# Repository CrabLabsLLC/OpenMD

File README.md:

# OpenMD

An Open Source Versatile Motor Driver powered by GaN

## Authors

[Orion Serup](orion@crablabs.io)

## Licensing

This project is licensed under the CERN Open Hardware License Version 2 - Weakly Reciprocal.

Different licensing can be provided for a nominal fee to allow for private spins of the design, contact the authors for more information on cost and license options.

## Operational Parameters

These are the initial estimates for reasonable limits provided sufficient cooling and stable power.

- Operating Voltage: 7V-80V
- Operating Current: 70A
- Max Theoretical Power: 4kW
- Switching Frequency: 50kHz-150KHz

## Purchasing

As of now this product is in Beta and thus is not publicly available for sale. Pre-production units may be available for evaluation, contact the authors for more information.

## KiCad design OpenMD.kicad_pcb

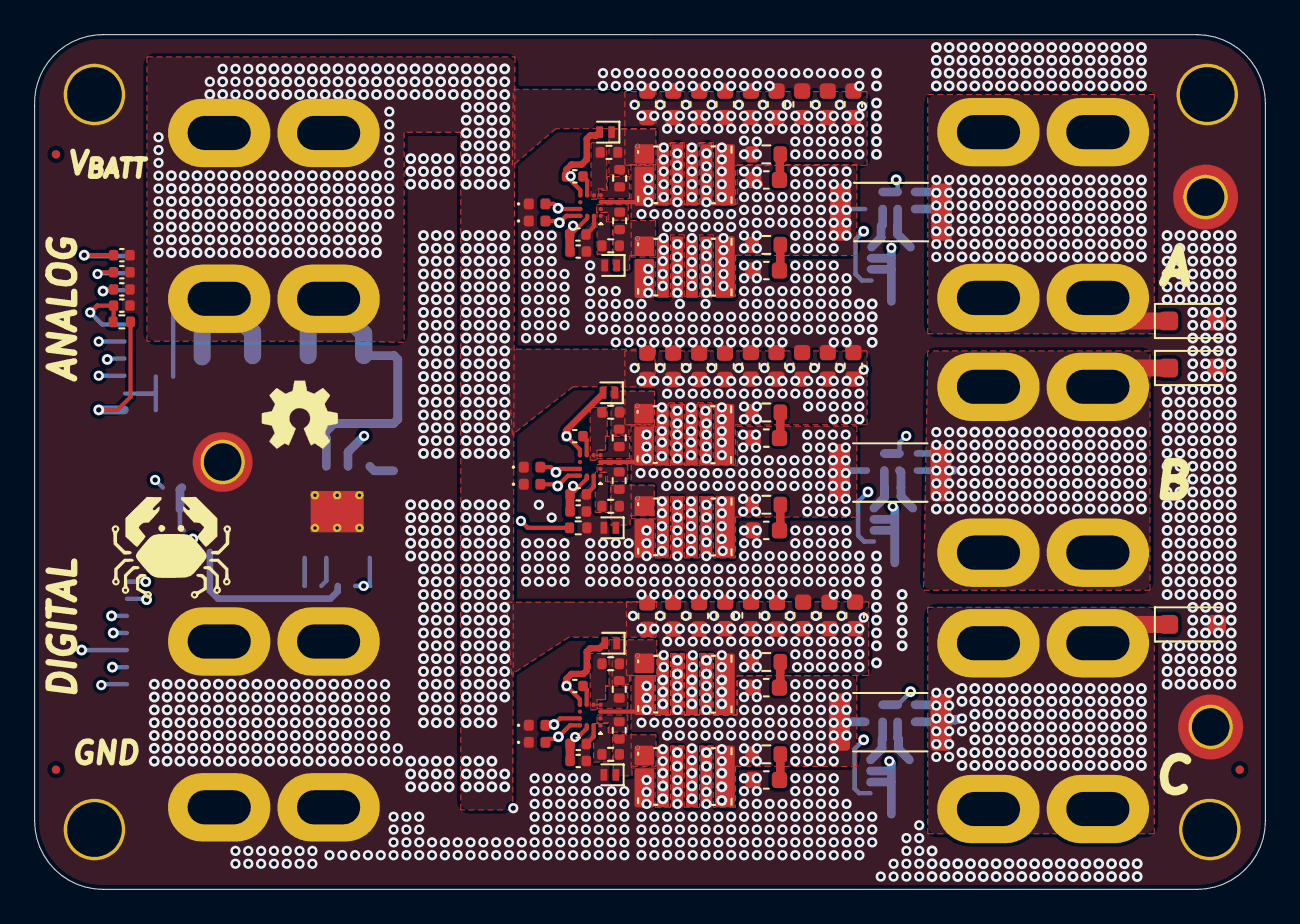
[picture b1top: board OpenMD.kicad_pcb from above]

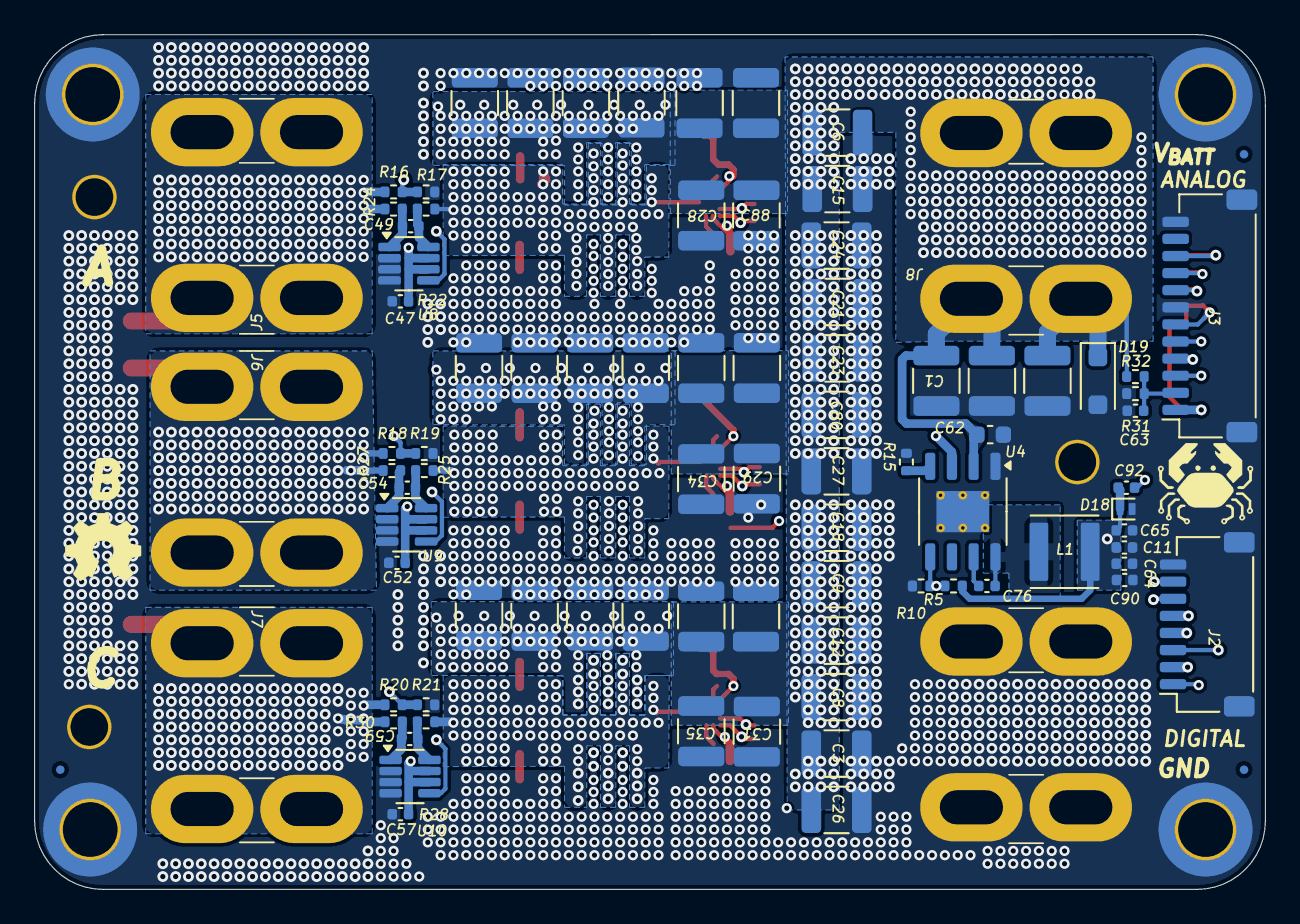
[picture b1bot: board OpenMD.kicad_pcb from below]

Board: 6 copper layers, 72.0 x 50.0 mm, 193 parts (93 on the bottom side), 62 nets.

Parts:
C1, C2, C3, C6, C7, C8, C9, C12, C15, C18, C19, C21, C23, C24, C26, C27, C78, C79, C80, C81, C82, C86, C87, C88, C89, C91, C93, C94, C98, C99, C100, C101, C102, C103: 10uF; C_1210_3225Metric
C4, C5, C10, C13, C14, C16, C17, C20, C22, C25, C30, C33, C36, C46, C48, C50, C51, C53, C55, C58, C60, C62, C70, C71, C72, C73, C74, C75: 100nF; C_0603_1608Metric
C11, C38, C39, C41, C42, C44, C45, C47, C52, C57, C63, C77: 100nF; C_0402_1005Metric
C28, C29, C31, C32, C34, C35: 4.7uF; C_1210_3225Metric
C37, C40, C43, C64, C65, C90: 4.7uF; C_0402_1005Metric
C49, C54, C59, C67, C68, C69: 10nF; C_0402_1005Metric
C56, C61, C66, C83, C84, C85: C; C_0603_1608Metric
C76: 2.2nF; C_0402_1005Metric
C92: 20pF; C_0402_1005Metric
D7, D8, D9, D19: 100V; D_SOD-123F
D12, D13, D14, D15, D16, D17: 5V; D_0402_1005Metric
D18, D27, D28, D29, D30, D31, D32: 6V; D_SOD-882
FID1, FID2, FID3, FID4, FID5, FID6: Fiducial; Fiducial_0.5mm_Mask1mm
H1, H2, H3, H4: M3; MountingHole_3.2mm_M3_ISO14580_Pad_TopOnly
H5: M2; MountingHole_2.2mm_M2_ISO7380_Pad_TopOnly
H6, H7: M2; MountingHole_2.2mm_M2_DIN965_Pad_TopOnly
J1: GND; DIP-4_252
J2: Digital; JST_SH_SM08B-SRSS-TB_1x08-1MP_P1.00mm_Horizontal
J3: Analog; JST_SH_SM12B-SRSS-TB_1x12-1MP_P1.00mm_Horizontal
J5: A; DIP-4_252
J6: B; DIP-4_252
J7: C; DIP-4_252
J8: V_{BATT}; DIP-4_252
L1: 68uH; L_Abracon_ASPI-4030S
Q1, Q2, Q3, Q4, Q5, Q6: EPC2361; D0606F_100V
R1, R4, R6, R9, R11, R14: 1; R_0402_1005Metric
R2, R3, R7, R8, R12, R13: 0; R_0402_1005Metric
R5, R16, R18, R20, R32: 240k; R_0402_1005Metric
R10: 72k; R_0402_1005Metric
R15: 27k; R_0402_1005Metric
R17, R19, R21, R31, R34: 10k; R_0402_1005Metric
R22, R24, R25, R27, R28, R30: 10; R_0402_1005Metric
R23, R26, R29: .5m; R_2512_6332Metric
R38, R39, R40, R41, R42, R43: R; R_0603_1608Metric
SYM1, SYM1#2: Logo_Open_Hardware_Large; OSHW-Symbol_8.9x8mm_SilkScreen
TH1: 10k NTC; R_0402_1005Metric
U1, U2, U3: LM1205; WLCSP1.6x1.6-12B_ECC
U4: LM5164DDA; HSOP-8-1EP_3.9x4.9mm_P1.27mm_EP2.41x3.1mm_ThermalVias
U8, U9, U10: INA241A2; SOT-23-8

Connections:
/A: D7.1 (K), J5.1, R16.1, R23.2, R24.1
/AH: D27.1 (K), Q4.1 (G), R3.2, R4.2
/AL: D30.1 (K), Q1.1 (G), R1.2, R2.1
/B: D8.1 (K), J6.1, R18.1, R26.2, R27.1
/BATT_SENSE: C63.1, J3.2, R31.1, R32.2
/BH: D28.1 (K), Q5.1 (G), R8.2, R9.2
/BL: D31.1 (K), Q2.1 (G), R6.2, R7.1
/C: D9.1 (K), J7.1, R20.1, R29.2, R30.1
/CH: D29.1 (K), Q6.1 (G), R13.2, R14.2
/CL: D32.1 (K), Q3.1 (G), R11.2, R12.1
/DRV_TEMP_SENSE: C77.1, J3.6, R34.2, TH1.1
/ENABLE: J2.1, U4.3 (EN/UVLO)
/GND: C1.2, C2.2, C3.2, C4.2, C5.2, C6.2, C7.2, C8.2, C9.2, C10.2, C11.2, C12.2, C13.2, C14.2, C15.2, C16.2, C17.2, C18.2, C19.2, C20.2, C21.2, C22.2, C23.2, C24.2, C25.2, C26.2, C27.2, C28.2, C29.2, C30.2, C31.2, C32.2, C33.2, C34.2, C35.2, C36.2, C37.2, C38.2, C40.2, C41.2, C43.2, C44.2, C46.2, C47.2, C48.2, C50.2, C51.2, C52.2, C53.2, C55.2, C57.2, C58.2, C60.2, C62.2, C63.2, C64.2, C65.2, C67.2, C68.2, C69.2, C70.2, C71.2, C72.2, C73.2, C74.2, C75.2, C77.2, C78.2, C79.2, C80.2, C81.2, C82.2, C83.2, C84.2, C85.2, C86.2, C87.2, C88.2, C89.2, C90.2, C91.2, C93.2, C94.2, C98.2, C99.2, C100.2, C101.2, C102.2, C103.2, D7.2 (A), D8.2 (A), D9.2 (A), D12.1 (A1), D13.1 (A1), D14.1 (A1), D15.1 (A1), D16.1 (A1), D17.1 (A1), D18.2 (A), D19.2 (A), D30.2 (A), D31.2 (A), D32.2 (A), H1.1, H2.1, H3.1, H4.1, H5.1, H6.1, H7.1, J1.1, J2.8, J2.MP (MountPin), J3.7, J3.12, J3.MP (MountPin), Q1.2 (S), Q1.4 (S), Q1.6 (S), Q2.2 (S), Q2.4 (S), Q2.6 (S), Q3.2 (S), Q3.4 (S), Q3.6 (S), R10.2, R15.2, R17.2, R19.2, R21.2, R31.2, TH1.2, U1.A2 (GND), U2.A2 (GND), U3.A2 (GND), U4.1 (GND), U4.9 (EP), U8.2 (GND), U8.3 (REF2), U8.4 (GND), U9.2 (GND), U9.3 (REF2), U9.4 (GND), U10.2 (GND), U10.3 (REF2), U10.4 (GND)
/INPUT.AH: D12.2 (A2), J2.3, U1.B4 (HI)
/INPUT.AL: D15.2 (A2), J2.2, U1.A4 (LI)
/INPUT.BH: D13.2 (A2), J2.5, U2.B4 (HI)
/INPUT.BL: D16.2 (A2), J2.4, U2.A4 (LI)
/INPUT.CH: D14.2 (A2), J2.7, U3.B4 (HI)
/INPUT.CL: D17.2 (A2), J2.6, U3.A4 (LI)
/I_SENSE.A: J3.3, U8.5
/I_SENSE.B: J3.4, U9.5
/I_SENSE.C: J3.5, U10.5
/Phase Current Sensors/Current Sense A/V+: C49.1, R22.2, U8.8 (+)
/Phase Current Sensors/Current Sense A/V-: C49.2, R24.2, U8.1 (-)
/Phase Current Sensors/Current Sense B/V+: C54.1, R25.2, U9.8 (+)
/Phase Current Sensors/Current Sense B/V-: C54.2, R27.2, U9.1 (-)
/Phase Current Sensors/Current Sense C/V+: C59.1, R28.2, U10.8 (+)
/Phase Current Sensors/Current Sense C/V-: C59.2, R30.2, U10.1 (-)
/Predriver Voltage Supply/FB: C92.2, R5.2, R10.1, U4.5 (FB)
/Predriver Voltage Supply/SW: C76.2, L1.1, U4.8 (SW)
/Predrivers/Gate Driver A/BOOT: C39.1, U1.D3 (BOOT)
/Predrivers/Gate Driver A/LGH: R1.1, U1.B1 (LGH)
/Predrivers/Gate Driver A/LGL: R2.2, U1.A1 (LGL)
/Predrivers/Gate Driver A/UGH: R4.1, U1.D2 (UGH)
/Predrivers/Gate Driver A/UGL: R3.1, U1.D1 (UGL)
/Predrivers/Gate Driver B/BOOT: C42.1, U2.D3 (BOOT)
/Predrivers/Gate Driver B/LGH: R6.1, U2.B1 (LGH)
/Predrivers/Gate Driver B/LGL: R7.2, U2.A1 (LGL)
/Predrivers/Gate Driver B/UGH: R9.1, U2.D2 (UGH)
/Predrivers/Gate Driver B/UGL: R8.1, U2.D1 (UGL)
/Predrivers/Gate Driver C/BOOT: C45.1, U3.D3 (BOOT)
/Predrivers/Gate Driver C/LGH: R11.1, U3.B1 (LGH)
/Predrivers/Gate Driver C/LGL: R12.2, U3.A1 (LGL)
/Predrivers/Gate Driver C/UGH: R14.1, U3.D2 (UGH)
/Predrivers/Gate Driver C/UGL: R13.1, U3.D1 (UGL)
/SW.A: C39.2, C56.2, D27.2 (A), Q1.3 (D), Q1.5 (D), Q1.7 (D), Q4.2 (S), Q4.4 (S), Q4.6 (S), R22.1, R23.1, R41.1, U1.C1 (PHASE), U1.D4 (PHASE)
/SW.B: C42.2, C61.2, D28.2 (A), Q2.3 (D), Q2.5 (D), Q2.7 (D), Q5.2 (S), Q5.4 (S), Q5.6 (S), R25.1, R26.1, R42.1, U2.C1 (PHASE), U2.D4 (PHASE)
/SW.C: C45.2, C66.2, D29.2 (A), Q3.3 (D), Q3.5 (D), Q3.7 (D), Q6.2 (S), Q6.4 (S), Q6.6 (S), R28.1, R29.1, R43.1, U3.C1 (PHASE), U3.D4 (PHASE)
/V_SENSE.A: C67.1, J3.8, R16.2, R17.1
/V_SENSE.B: C68.1, J3.9, R18.2, R19.1
/V_SENSE.C: C69.1, J3.10, R20.2, R21.1
/V_{ANA}: C47.1, C52.1, C57.1, J3.1, R34.1, U8.6 (V+), U8.7 (REF1), U9.6 (V+), U9.7 (REF1), U10.6 (V+), U10.7 (REF1)
/V_{BATT}: C1.1, C2.1, C3.1, C4.1, C5.1, C6.1, C7.1, C8.1, C9.1, C10.1, C12.1, C13.1, C14.1, C15.1, C16.1, C17.1, C18.1, C19.1, C20.1, C21.1, C22.1, C23.1, C24.1, C25.1, C26.1, C27.1, C28.1, C29.1, C30.1, C31.1, C32.1, C33.1, C34.1, C35.1, C36.1, C46.1, C48.1, C50.1, C51.1, C53.1, C55.1, C58.1, C60.1, C62.1, C70.1, C71.1, C72.1, C73.1, C74.1, C75.1, C78.1, C79.1, C80.1, C81.1, C82.1, C86.1, C87.1, C88.1, C89.1, C91.1, C93.1, C94.1, C98.1, C99.1, C100.1, C101.1, C102.1, C103.1, D19.1 (K), J8.1, Q4.3 (D), Q4.5 (D), Q4.7 (D), Q5.3 (D), Q5.5 (D), Q5.7 (D), Q6.3 (D), Q6.5 (D), Q6.7 (D), R32.1, R38.1, R39.1, R40.1, U4.2 (VIN)
/V_{DRV}: C11.1, C37.1, C38.1, C40.1, C41.1, C43.1, C44.1, C64.1, C65.1, C90.1, C92.1, D18.1 (K), L1.2, R5.1, U1.A3 (VCC), U2.A3 (VCC), U3.A3 (VCC)
unnamed: C56.1, R38.2
unnamed: C61.1, R39.2
unnamed: C66.1, R40.2
unnamed: C83.1, R41.2
unnamed: C84.1, R42.2
unnamed: C85.1, R43.2
unnamed: C76.1, U4.7 (BST)
unnamed: R15.1, U4.4 (RON)

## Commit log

2024-05-19 first revision
2024-05-20 added license and almost ready for prod
2024-06-05 first fab run
2024-06-05 Production round 1
2024-06-06 added docs
2024-06-06 added ESD protection
2024-06-06 add context
2024-06-08 more powerful version
2024-06-09 adjusted according to Reddit feedback
    Still needs TVS adjusted
2024-06-09 added all changes from Reddit
2024-06-18 Removed Hall Sensors for Scalability
2024-06-19 updates to make better
2024-06-19 cleanup
2024-06-22 Tidying things up
2024-06-22 moved amps to back
2024-06-23 fixed grounding issues
2024-06-23 update fab layers
2024-07-05 revision 2
2024-07-21 add heatspreader
2024-08-31 next generation
2024-08-31 updated docs
2024-09-06 update docs
2024-12-19 added more capacitance
2024-12-20 fixes

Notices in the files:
OpenMD.kicad_pcb:
License: CERN-OHL-W-2.0
